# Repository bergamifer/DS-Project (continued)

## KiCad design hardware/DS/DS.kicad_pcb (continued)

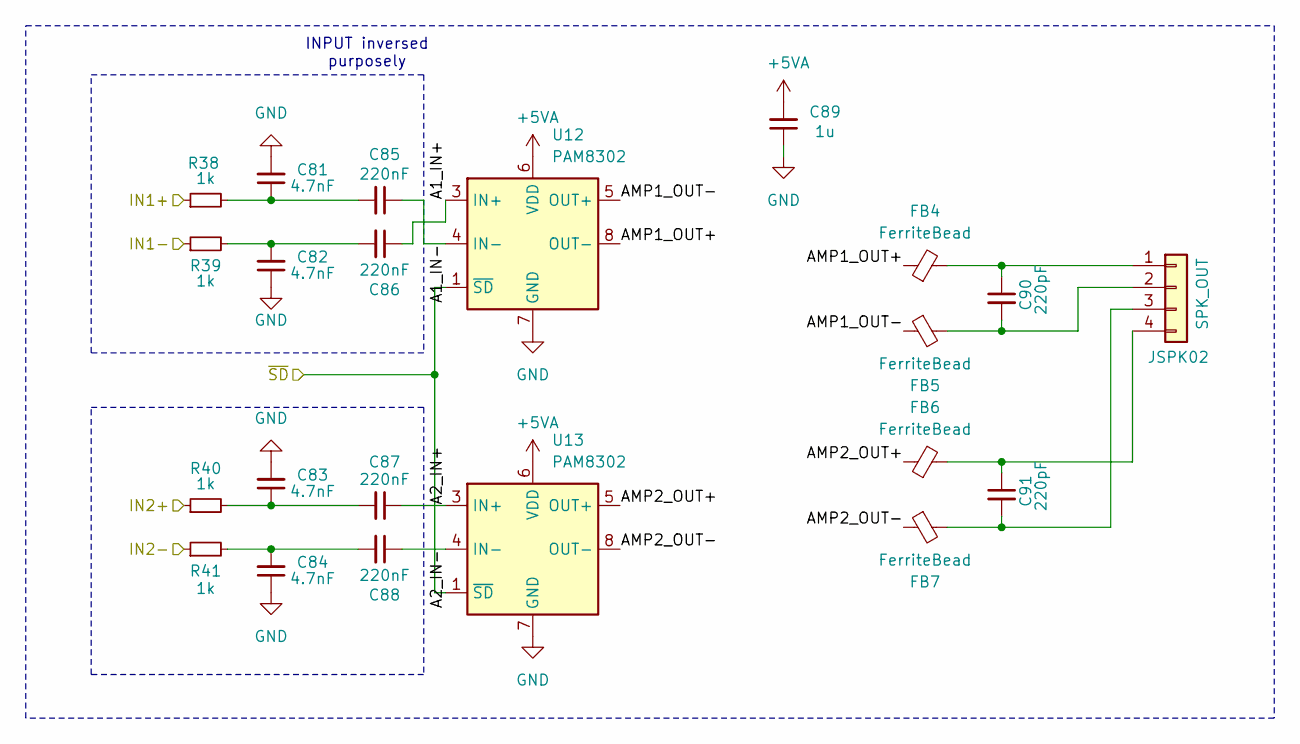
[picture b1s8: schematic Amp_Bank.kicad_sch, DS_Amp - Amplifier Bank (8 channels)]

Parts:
C81, C82, C83, C84: 4.7nF; C_0603_1608Metric; Manufacturer_Part_Number GCM1885C1H472GA16D; LCSC C2961271
C85, C86, C87, C88: 220nF; C_0402_1005Metric; Manufacturer_Part_Number CL05B224KO5NNNC; LCSC C16772
C89: 1u; C_0603_1608Metric; Mouser part 791-0603B105M160CT
C90, C91: 220pF; C_0402_1005Metric; Mouser part 581-KGM15BR71E104KT
FB4, FB5, FB6, FB7: FerriteBead; L_0805_2012Metric; Manufacturer_Part_Number SCBW201209U601T; LCSC C21286
JSPK02: SPK_OUT; JST_XH_B4B-XH-A_1x04_P2.50mm_Vertical; Manufacturer_Part_Number 8821WV-04KP; LCSC C5447988
R38, R39, R40, R41: 1k; R_0402_1005Metric; Manufacturer_Part_Number 0402WGF1001TCE; LCSC C11702
U12, U13: PAM8302; MSOP-8_3x3mm_P0.65mm; Manufacturer_Part_Number PAM8302AASCR; LCSC C113367

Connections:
+5VA: C89.2, U12.6 (VDD), U13.6 (VDD); also elsewhere on the board
/ALL_AMPS/Amp_Bank_A1/A1_IN+: C86.1, U12.3 (IN+)
/ALL_AMPS/Amp_Bank_A1/A1_IN-: C85.1, U12.4 (IN-)
/ALL_AMPS/Amp_Bank_A1/A2_IN+: C87.1, U13.3 (IN+)
/ALL_AMPS/Amp_Bank_A1/A2_IN-: C88.1, U13.4 (IN-)
/ALL_AMPS/Amp_Bank_A1/AMP1_OUT+: FB4.1, U12.8 (OUT-)
/ALL_AMPS/Amp_Bank_A1/AMP1_OUT-: FB5.1, U12.5 (OUT+)
/ALL_AMPS/Amp_Bank_A1/AMP2_OUT+: FB6.1, U13.5 (OUT+)
/ALL_AMPS/Amp_Bank_A1/AMP2_OUT-: FB7.1, U13.8 (OUT-)
/ALL_AMPS/SD: U12.1 (~SD), U13.1 (~SD); also elsewhere on the board
/ALL_AMPS/VA.N3: R39.1; also elsewhere on the board
/ALL_AMPS/VA.N4: R41.1; also elsewhere on the board
/ALL_AMPS/VA.P3: R38.1; also elsewhere on the board
/ALL_AMPS/VA.P4: R40.1; also elsewhere on the board
GND: C81.2, C82.1, C83.2, C84.1, C89.1, U12.7 (GND), U13.7 (GND); also elsewhere on the board
unnamed: C81.1, C85.2, R38.2
unnamed: C82.2, C86.2, R39.2
unnamed: C83.1, C87.2, R40.2
unnamed: C84.2, C88.2, R41.2
unnamed: C90.1, FB4.2, JSPK02.1
unnamed: C90.2, FB5.2, JSPK02.2
unnamed: C91.2, FB7.2, JSPK02.3
unnamed: C91.1, FB6.2, JSPK02.4

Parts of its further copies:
C92, C93, C94, C95, C103, C104, C105, C106, C114, C115, C116, C117, C125, C126, C127, C128, C136, C137, C138, C139, C147, C148, C149, C150, C158, C159, C160, C161, C169, C170, C171, C172, C180, C181, C182, C183, C191, C192, C193, C194, C202, C203, C204, C205, C213, C214, C215, C216, C224, C225, C226, C227, C235, C236, C237, C238, C246, C247, C248, C249: 4.7nF; C_0603_1608Metric; Manufacturer_Part_Number GCM1885C1H472GA16D; LCSC C2961271
C96, C97, C98, C99, C107, C108, C109, C110, C118, C119, C120, C121, C129, C130, C131, C132, C140, C141, C142, C143, C151, C152, C153, C154, C162, C163, C164, C165, C173, C174, C175, C176, C184, C185, C186, C187, C195, C196, C197, C198, C206, C207, C208, C209, C217, C218, C219, C220, C228, C229, C230, C231, C239, C240, C241, C242, C250, C251, C252, C253: 220nF; C_0402_1005Metric; Manufacturer_Part_Number CL05B224KO5NNNC; LCSC C16772
C100, C111, C122, C133, C144, C155, C166, C177, C188, C199, C210, C221, C232, C243, C254: 1u; C_0603_1608Metric; Mouser part 791-0603B105M160CT
C101, C102, C112, C113, C123, C124, C134, C135, C145, C146, C156, C157, C167, C168, C178, C179, C189, C190, C200, C201, C211, C212, C222, C223, C233, C234, C244, C245, C255, C256: 220pF; C_0402_1005Metric; Mouser part 581-KGM15BR71E104KT
FB8, FB9, FB10, FB11, FB12, FB13, FB14, FB15, FB16, FB17, FB18, FB19, FB20, FB21, FB22, FB23, FB24, FB25, FB26, FB27, FB28, FB29, FB30, FB31, FB32, FB33, FB34, FB35, FB36, FB37, FB38, FB39, FB40, FB41, FB42, FB43, FB44, FB45, FB46, FB47, FB48, FB49, FB50, FB51, FB52, FB53, FB54, FB55, FB56, FB57, FB58, FB59, FB60, FB61, FB62, FB63, FB64, FB65, FB66, FB67: FerriteBead; L_0805_2012Metric; Manufacturer_Part_Number SCBW201209U601T; LCSC C21286
JSPK01, JSPK03, JSPK04, JSPK05, JSPK06, JSPK07, JSPK08, JSPK09, JSPK10, JSPK11, JSPK12, JSPK13, JSPK14, JSPK15, JSPK16: SPK_OUT; JST_XH_B4B-XH-A_1x04_P2.50mm_Vertical; Manufacturer_Part_Number 8821WV-04KP; LCSC C5447988
R42, R43, R44, R45, R46, R47, R48, R49, R50, R51, R52, R53, R54, R55, R56, R57, R58, R59, R60, R61, R62, R63, R64, R65, R66, R67, R68, R69, R70, R71, R72, R73, R74, R75, R76, R77, R78, R79, R80, R81, R82, R83, R84, R85, R86, R87, R88, R89, R90, R91, R92, R93, R94, R95, R96, R97, R98, R99, R100, R101: 1k; R_0402_1005Metric; Manufacturer_Part_Number 0402WGF1001TCE; LCSC C11702
U14, U15, U16, U17, U18, U19, U20, U21, U22, U23, U24, U25, U26, U27, U28, U29, U30, U31, U32, U33, U34, U35, U36, U37, U38, U39, U40, U41, U42, U43: PAM8302; MSOP-8_3x3mm_P0.65mm; Manufacturer_Part_Number PAM8302AASCR; LCSC C113367

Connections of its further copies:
+5VA: C100.2, C111.2, C122.2, C133.2, C144.2, C155.2, C166.2, C177.2, C188.2, C199.2, C210.2, C221.2, C232.2, C243.2, C254.2, U14.6 (VDD), U15.6 (VDD), U16.6 (VDD), U17.6 (VDD), U18.6 (VDD), U19.6 (VDD), U20.6 (VDD), U21.6 (VDD), U22.6 (VDD), U23.6 (VDD), U24.6 (VDD), U25.6 (VDD), U26.6 (VDD), U27.6 (VDD), U28.6 (VDD), U29.6 (VDD), U30.6 (VDD), U31.6 (VDD), U32.6 (VDD), U33.6 (VDD), U34.6 (VDD), U35.6 (VDD), U36.6 (VDD), U37.6 (VDD), U38.6 (VDD), U39.6 (VDD), U40.6 (VDD), U41.6 (VDD), U42.6 (VDD), U43.6 (VDD); also elsewhere on the board
/ALL_AMPS/Amp_Bank_A2/A1_IN+: C97.1, U14.3 (IN+)
/ALL_AMPS/Amp_Bank_A2/A1_IN-: C96.1, U14.4 (IN-)
/ALL_AMPS/Amp_Bank_A2/A2_IN+: C98.1, U15.3 (IN+)
/ALL_AMPS/Amp_Bank_A2/A2_IN-: C99.1, U15.4 (IN-)
/ALL_AMPS/Amp_Bank_A2/AMP1_OUT+: FB8.1, U14.8 (OUT-)
/ALL_AMPS/Amp_Bank_A2/AMP1_OUT-: FB9.1, U14.5 (OUT+)
/ALL_AMPS/Amp_Bank_A2/AMP2_OUT+: FB10.1, U15.5 (OUT+)
/ALL_AMPS/Amp_Bank_A2/AMP2_OUT-: FB11.1, U15.8 (OUT-)
/ALL_AMPS/Amp_Bank_A3/A1_IN+: C108.1, U16.3 (IN+)
/ALL_AMPS/Amp_Bank_A3/A1_IN-: C107.1, U16.4 (IN-)
/ALL_AMPS/Amp_Bank_A3/A2_IN+: C109.1, U17.3 (IN+)
/ALL_AMPS/Amp_Bank_A3/A2_IN-: C110.1, U17.4 (IN-)
/ALL_AMPS/Amp_Bank_A3/AMP1_OUT+: FB12.1, U16.8 (OUT-)
/ALL_AMPS/Amp_Bank_A3/AMP1_OUT-: FB13.1, U16.5 (OUT+)
/ALL_AMPS/Amp_Bank_A3/AMP2_OUT+: FB14.1, U17.5 (OUT+)
/ALL_AMPS/Amp_Bank_A3/AMP2_OUT-: FB15.1, U17.8 (OUT-)
/ALL_AMPS/Amp_Bank_A4/A1_IN+: C119.1, U18.3 (IN+)
/ALL_AMPS/Amp_Bank_A4/A1_IN-: C118.1, U18.4 (IN-)
/ALL_AMPS/Amp_Bank_A4/A2_IN+: C120.1, U19.3 (IN+)
/ALL_AMPS/Amp_Bank_A4/A2_IN-: C121.1, U19.4 (IN-)
/ALL_AMPS/Amp_Bank_A4/AMP1_OUT+: FB16.1, U18.8 (OUT-)
/ALL_AMPS/Amp_Bank_A4/AMP1_OUT-: FB17.1, U18.5 (OUT+)
/ALL_AMPS/Amp_Bank_A4/AMP2_OUT+: FB18.1, U19.5 (OUT+)
/ALL_AMPS/Amp_Bank_A4/AMP2_OUT-: FB19.1, U19.8 (OUT-)
/ALL_AMPS/Amp_Bank_A5/A1_IN+: C130.1, U20.3 (IN+)
/ALL_AMPS/Amp_Bank_A5/A1_IN-: C129.1, U20.4 (IN-)
/ALL_AMPS/Amp_Bank_A5/A2_IN+: C131.1, U21.3 (IN+)
/ALL_AMPS/Amp_Bank_A5/A2_IN-: C132.1, U21.4 (IN-)
/ALL_AMPS/Amp_Bank_A5/AMP1_OUT+: FB20.1, U20.8 (OUT-)
/ALL_AMPS/Amp_Bank_A5/AMP1_OUT-: FB21.1, U20.5 (OUT+)
/ALL_AMPS/Amp_Bank_A5/AMP2_OUT+: FB22.1, U21.5 (OUT+)
/ALL_AMPS/Amp_Bank_A5/AMP2_OUT-: FB23.1, U21.8 (OUT-)
/ALL_AMPS/Amp_Bank_A6/A1_IN+: C141.1, U22.3 (IN+)
/ALL_AMPS/Amp_Bank_A6/A1_IN-: C140.1, U22.4 (IN-)
/ALL_AMPS/Amp_Bank_A6/A2_IN+: C142.1, U23.3 (IN+)
/ALL_AMPS/Amp_Bank_A6/A2_IN-: C143.1, U23.4 (IN-)
/ALL_AMPS/Amp_Bank_A6/AMP1_OUT+: FB24.1, U22.8 (OUT-)
/ALL_AMPS/Amp_Bank_A6/AMP1_OUT-: FB25.1, U22.5 (OUT+)
/ALL_AMPS/Amp_Bank_A6/AMP2_OUT+: FB26.1, U23.5 (OUT+)
/ALL_AMPS/Amp_Bank_A6/AMP2_OUT-: FB27.1, U23.8 (OUT-)
/ALL_AMPS/Amp_Bank_A7/A1_IN+: C152.1, U24.3 (IN+)
/ALL_AMPS/Amp_Bank_A7/A1_IN-: C151.1, U24.4 (IN-)
/ALL_AMPS/Amp_Bank_A7/A2_IN+: C153.1, U25.3 (IN+)
/ALL_AMPS/Amp_Bank_A7/A2_IN-: C154.1, U25.4 (IN-)
/ALL_AMPS/Amp_Bank_A7/AMP1_OUT+: FB28.1, U24.8 (OUT-)
/ALL_AMPS/Amp_Bank_A7/AMP1_OUT-: FB29.1, U24.5 (OUT+)
/ALL_AMPS/Amp_Bank_A7/AMP2_OUT+: FB30.1, U25.5 (OUT+)
/ALL_AMPS/Amp_Bank_A7/AMP2_OUT-: FB31.1, U25.8 (OUT-)
/ALL_AMPS/Amp_Bank_A8/A1_IN+: C163.1, U26.3 (IN+)
/ALL_AMPS/Amp_Bank_A8/A1_IN-: C162.1, U26.4 (IN-)
/ALL_AMPS/Amp_Bank_A8/A2_IN+: C164.1, U27.3 (IN+)
/ALL_AMPS/Amp_Bank_A8/A2_IN-: C165.1, U27.4 (IN-)
/ALL_AMPS/Amp_Bank_A8/AMP1_OUT+: FB32.1, U26.8 (OUT-)
/ALL_AMPS/Amp_Bank_A8/AMP1_OUT-: FB33.1, U26.5 (OUT+)
/ALL_AMPS/Amp_Bank_A8/AMP2_OUT+: FB34.1, U27.5 (OUT+)
/ALL_AMPS/Amp_Bank_A8/AMP2_OUT-: FB35.1, U27.8 (OUT-)
/ALL_AMPS/Amp_Bank_A9/A1_IN+: C174.1, U28.3 (IN+)
/ALL_AMPS/Amp_Bank_A9/A1_IN-: C173.1, U28.4 (IN-)
/ALL_AMPS/Amp_Bank_A9/A2_IN+: C175.1, U29.3 (IN+)
/ALL_AMPS/Amp_Bank_A9/A2_IN-: C176.1, U29.4 (IN-)
/ALL_AMPS/Amp_Bank_A9/AMP1_OUT+: FB36.1, U28.8 (OUT-)
/ALL_AMPS/Amp_Bank_A9/AMP1_OUT-: FB37.1, U28.5 (OUT+)
/ALL_AMPS/Amp_Bank_A9/AMP2_OUT+: FB38.1, U29.5 (OUT+)
/ALL_AMPS/Amp_Bank_A9/AMP2_OUT-: FB39.1, U29.8 (OUT-)
/ALL_AMPS/Amp_Bank_A10/A1_IN+: C185.1, U30.3 (IN+)
/ALL_AMPS/Amp_Bank_A10/A1_IN-: C184.1, U30.4 (IN-)
/ALL_AMPS/Amp_Bank_A10/A2_IN+: C186.1, U31.3 (IN+)
/ALL_AMPS/Amp_Bank_A10/A2_IN-: C187.1, U31.4 (IN-)
/ALL_AMPS/Amp_Bank_A10/AMP1_OUT+: FB40.1, U30.8 (OUT-)
/ALL_AMPS/Amp_Bank_A10/AMP1_OUT-: FB41.1, U30.5 (OUT+)
/ALL_AMPS/Amp_Bank_A10/AMP2_OUT+: FB42.1, U31.5 (OUT+)
/ALL_AMPS/Amp_Bank_A10/AMP2_OUT-: FB43.1, U31.8 (OUT-)
/ALL_AMPS/Amp_Bank_A11/A1_IN+: C196.1, U32.3 (IN+)
/ALL_AMPS/Amp_Bank_A11/A1_IN-: C195.1, U32.4 (IN-)
/ALL_AMPS/Amp_Bank_A11/A2_IN+: C197.1, U33.3 (IN+)
/ALL_AMPS/Amp_Bank_A11/A2_IN-: C198.1, U33.4 (IN-)
/ALL_AMPS/Amp_Bank_A11/AMP1_OUT+: FB44.1, U32.8 (OUT-)
/ALL_AMPS/Amp_Bank_A11/AMP1_OUT-: FB45.1, U32.5 (OUT+)
/ALL_AMPS/Amp_Bank_A11/AMP2_OUT+: FB46.1, U33.5 (OUT+)
/ALL_AMPS/Amp_Bank_A11/AMP2_OUT-: FB47.1, U33.8 (OUT-)
/ALL_AMPS/Amp_Bank_A12/A1_IN+: C207.1, U34.3 (IN+)
/ALL_AMPS/Amp_Bank_A12/A1_IN-: C206.1, U34.4 (IN-)
/ALL_AMPS/Amp_Bank_A12/A2_IN+: C208.1, U35.3 (IN+)
/ALL_AMPS/Amp_Bank_A12/A2_IN-: C209.1, U35.4 (IN-)
/ALL_AMPS/Amp_Bank_A12/AMP1_OUT+: FB48.1, U34.8 (OUT-)
/ALL_AMPS/Amp_Bank_A12/AMP1_OUT-: FB49.1, U34.5 (OUT+)
/ALL_AMPS/Amp_Bank_A12/AMP2_OUT+: FB50.1, U35.5 (OUT+)
/ALL_AMPS/Amp_Bank_A12/AMP2_OUT-: FB51.1, U35.8 (OUT-)
/ALL_AMPS/Amp_Bank_A13/A1_IN+: C218.1, U36.3 (IN+)
/ALL_AMPS/Amp_Bank_A13/A1_IN-: C217.1, U36.4 (IN-)
/ALL_AMPS/Amp_Bank_A13/A2_IN+: C219.1, U37.3 (IN+)
/ALL_AMPS/Amp_Bank_A13/A2_IN-: C220.1, U37.4 (IN-)
/ALL_AMPS/Amp_Bank_A13/AMP1_OUT+: FB52.1, U36.8 (OUT-)
/ALL_AMPS/Amp_Bank_A13/AMP1_OUT-: FB53.1, U36.5 (OUT+)
/ALL_AMPS/Amp_Bank_A13/AMP2_OUT+: FB54.1, U37.5 (OUT+)
/ALL_AMPS/Amp_Bank_A13/AMP2_OUT-: FB55.1, U37.8 (OUT-)
/ALL_AMPS/Amp_Bank_A14/A1_IN+: C229.1, U38.3 (IN+)
/ALL_AMPS/Amp_Bank_A14/A1_IN-: C228.1, U38.4 (IN-)
/ALL_AMPS/Amp_Bank_A14/A2_IN+: C230.1, U39.3 (IN+)
/ALL_AMPS/Amp_Bank_A14/A2_IN-: C231.1, U39.4 (IN-)
/ALL_AMPS/Amp_Bank_A14/AMP1_OUT+: FB56.1, U38.8 (OUT-)
/ALL_AMPS/Amp_Bank_A14/AMP1_OUT-: FB57.1, U38.5 (OUT+)
/ALL_AMPS/Amp_Bank_A14/AMP2_OUT+: FB58.1, U39.5 (OUT+)
/ALL_AMPS/Amp_Bank_A14/AMP2_OUT-: FB59.1, U39.8 (OUT-)
/ALL_AMPS/Amp_Bank_A15/A1_IN+: C240.1, U40.3 (IN+)
/ALL_AMPS/Amp_Bank_A15/A1_IN-: C239.1, U40.4 (IN-)
/ALL_AMPS/Amp_Bank_A15/A2_IN+: C241.1, U41.3 (IN+)
/ALL_AMPS/Amp_Bank_A15/A2_IN-: C242.1, U41.4 (IN-)
/ALL_AMPS/Amp_Bank_A15/AMP1_OUT+: FB60.1, U40.8 (OUT-)
/ALL_AMPS/Amp_Bank_A15/AMP1_OUT-: FB61.1, U40.5 (OUT+)
/ALL_AMPS/Amp_Bank_A15/AMP2_OUT+: FB62.1, U41.5 (OUT+)
/ALL_AMPS/Amp_Bank_A15/AMP2_OUT-: FB63.1, U41.8 (OUT-)
/ALL_AMPS/Amp_Bank_A16/A1_IN+: C251.1, U42.3 (IN+)
/ALL_AMPS/Amp_Bank_A16/A1_IN-: C250.1, U42.4 (IN-)
/ALL_AMPS/Amp_Bank_A16/A2_IN+: C252.1, U43.3 (IN+)
/ALL_AMPS/Amp_Bank_A16/A2_IN-: C253.1, U43.4 (IN-)
/ALL_AMPS/Amp_Bank_A16/AMP1_OUT+: FB64.1, U42.8 (OUT-)
/ALL_AMPS/Amp_Bank_A16/AMP1_OUT-: FB65.1, U42.5 (OUT+)
/ALL_AMPS/Amp_Bank_A16/AMP2_OUT+: FB66.1, U43.5 (OUT+)
/ALL_AMPS/Amp_Bank_A16/AMP2_OUT-: FB67.1, U43.8 (OUT-)
/ALL_AMPS/SD: U14.1 (~SD), U15.1 (~SD), U16.1 (~SD), U17.1 (~SD), U18.1 (~SD), U19.1 (~SD), U20.1 (~SD), U21.1 (~SD), U22.1 (~SD), U23.1 (~SD), U24.1 (~SD), U25.1 (~SD), U26.1 (~SD), U27.1 (~SD), U28.1 (~SD), U29.1 (~SD), U30.1 (~SD), U31.1 (~SD), U32.1 (~SD), U33.1 (~SD), U34.1 (~SD), U35.1 (~SD), U36.1 (~SD), U37.1 (~SD), U38.1 (~SD), U39.1 (~SD), U40.1 (~SD), U41.1 (~SD), U42.1 (~SD), U43.1 (~SD); also elsewhere on the board
/ALL_AMPS/VA.N1: R99.1; also elsewhere on the board
/ALL_AMPS/VA.N2: R101.1; also elsewhere on the board
/ALL_AMPS/VA.N5: R43.1; also elsewhere on the board
/ALL_AMPS/VA.N6: R45.1; also elsewhere on the board
/ALL_AMPS/VA.N7: R47.1; also elsewhere on the board
/ALL_AMPS/VA.N8: R49.1; also elsewhere on the board
/ALL_AMPS/VA.P1: R98.1; also elsewhere on the board
/ALL_AMPS/VA.P2: R100.1; also elsewhere on the board
/ALL_AMPS/VA.P5: R42.1; also elsewhere on the board
/ALL_AMPS/VA.P6: R44.1; also elsewhere on the board
/ALL_AMPS/VA.P7: R46.1; also elsewhere on the board
/ALL_AMPS/VA.P8: R48.1; also elsewhere on the board
/ALL_AMPS/VB.N1: R51.1; also elsewhere on the board
/ALL_AMPS/VB.N2: R53.1; also elsewhere on the board
/ALL_AMPS/VB.N3: R55.1; also elsewhere on the board
/ALL_AMPS/VB.N4: R57.1; also elsewhere on the board
/ALL_AMPS/VB.N5: R59.1; also elsewhere on the board
/ALL_AMPS/VB.N6: R61.1; also elsewhere on the board
/ALL_AMPS/VB.N7: R63.1; also elsewhere on the board
/ALL_AMPS/VB.N8: R65.1; also elsewhere on the board
/ALL_AMPS/VB.P1: R50.1; also elsewhere on the board
/ALL_AMPS/VB.P2: R52.1; also elsewhere on the board
/ALL_AMPS/VB.P3: R54.1; also elsewhere on the board
/ALL_AMPS/VB.P4: R56.1; also elsewhere on the board
/ALL_AMPS/VB.P5: R58.1; also elsewhere on the board
/ALL_AMPS/VB.P6: R60.1; also elsewhere on the board
/ALL_AMPS/VB.P7: R62.1; also elsewhere on the board
/ALL_AMPS/VB.P8: R64.1; also elsewhere on the board
/ALL_AMPS/VC.N1: R67.1; also elsewhere on the board
/ALL_AMPS/VC.N2: R69.1; also elsewhere on the board
/ALL_AMPS/VC.N3: R71.1; also elsewhere on the board
/ALL_AMPS/VC.N4: R73.1; also elsewhere on the board
/ALL_AMPS/VC.N5: R75.1; also elsewhere on the board
/ALL_AMPS/VC.N6: R77.1; also elsewhere on the board
/ALL_AMPS/VC.N7: R79.1; also elsewhere on the board
/ALL_AMPS/VC.N8: R81.1; also elsewhere on the board
/ALL_AMPS/VC.P1: R66.1; also elsewhere on the board
/ALL_AMPS/VC.P2: R68.1; also elsewhere on the board
/ALL_AMPS/VC.P3: R70.1; also elsewhere on the board
/ALL_AMPS/VC.P4: R72.1; also elsewhere on the board
/ALL_AMPS/VC.P5: R74.1; also elsewhere on the board
/ALL_AMPS/VC.P6: R76.1; also elsewhere on the board
/ALL_AMPS/VC.P7: R78.1; also elsewhere on the board
/ALL_AMPS/VC.P8: R80.1; also elsewhere on the board
/ALL_AMPS/VD.N1: R83.1; also elsewhere on the board
/ALL_AMPS/VD.N2: R85.1; also elsewhere on the board
/ALL_AMPS/VD.N3: R87.1; also elsewhere on the board
/ALL_AMPS/VD.N4: R89.1; also elsewhere on the board
/ALL_AMPS/VD.N5: R91.1; also elsewhere on the board
/ALL_AMPS/VD.N6: R93.1; also elsewhere on the board
/ALL_AMPS/VD.N7: R95.1; also elsewhere on the board
/ALL_AMPS/VD.N8: R97.1; also elsewhere on the board
/ALL_AMPS/VD.P1: R82.1; also elsewhere on the board
/ALL_AMPS/VD.P2: R84.1; also elsewhere on the board
/ALL_AMPS/VD.P3: R86.1; also elsewhere on the board
/ALL_AMPS/VD.P4: R88.1; also elsewhere on the board
/ALL_AMPS/VD.P5: R90.1; also elsewhere on the board
/ALL_AMPS/VD.P6: R92.1; also elsewhere on the board
/ALL_AMPS/VD.P7: R94.1; also elsewhere on the board
/ALL_AMPS/VD.P8: R96.1; also elsewhere on the board
GND: C92.2, C93.1, C94.2, C95.1, C100.1, C103.2, C104.1, C105.2, C106.1, C111.1, C114.2, C115.1, C116.2, C117.1, C122.1, C125.2, C126.1, C127.2, C128.1, C133.1, C136.2, C137.1, C138.2, C139.1, C144.1, C147.2, C148.1, C149.2, C150.1, C155.1, C158.2, C159.1, C160.2, C161.1, C166.1, C169.2, C170.1, C171.2, C172.1, C177.1, C180.2, C181.1, C182.2, C183.1, C188.1, C191.2, C192.1, C193.2, C194.1, C199.1, C202.2, C203.1, C204.2, C205.1, C210.1, C213.2, C214.1, C215.2, C216.1, C221.1, C224.2, C225.1, C226.2, C227.1, C232.1, C235.2, C236.1, C237.2, C238.1, C243.1, C246.2, C247.1, C248.2, C249.1, C254.1, U14.7 (GND), U15.7 (GND), U16.7 (GND), U17.7 (GND), U18.7 (GND), U19.7 (GND), U20.7 (GND), U21.7 (GND), U22.7 (GND), U23.7 (GND), U24.7 (GND), U25.7 (GND), U26.7 (GND), U27.7 (GND), U28.7 (GND), U29.7 (GND), U30.7 (GND), U31.7 (GND), U32.7 (GND), U33.7 (GND), U34.7 (GND), U35.7 (GND), U36.7 (GND), U37.7 (GND), U38.7 (GND), U39.7 (GND), U40.7 (GND), U41.7 (GND), U42.7 (GND), U43.7 (GND); also elsewhere on the board
unnamed: C92.1, C96.2, R42.2
unnamed: C93.2, C97.2, R43.2
unnamed: C94.1, C98.2, R44.2
unnamed: C95.2, C99.2, R45.2
unnamed: C103.1, C107.2, R46.2
unnamed: C104.2, C108.2, R47.2
unnamed: C105.1, C109.2, R48.2
unnamed: C106.2, C110.2, R49.2
unnamed: C114.1, C118.2, R50.2
unnamed: C115.2, C119.2, R51.2
unnamed: C116.1, C120.2, R52.2
unnamed: C117.2, C121.2, R53.2
unnamed: C125.1, C129.2, R54.2
unnamed: C126.2, C130.2, R55.2
unnamed: C127.1, C131.2, R56.2
unnamed: C128.2, C132.2, R57.2
unnamed: C136.1, C140.2, R58.2
unnamed: C137.2, C141.2, R59.2
unnamed: C138.1, C142.2, R60.2
unnamed: C139.2, C143.2, R61.2
unnamed: C147.1, C151.2, R62.2
unnamed: C148.2, C152.2, R63.2
unnamed: C149.1, C153.2, R64.2
unnamed: C150.2, C154.2, R65.2
unnamed: C158.1, C162.2, R66.2
unnamed: C159.2, C163.2, R67.2
unnamed: C160.1, C164.2, R68.2
unnamed: C161.2, C165.2, R69.2
unnamed: C169.1, C173.2, R70.2
unnamed: C170.2, C174.2, R71.2
unnamed: C171.1, C175.2, R72.2
unnamed: C172.2, C176.2, R73.2
unnamed: C180.1, C184.2, R74.2
unnamed: C181.2, C185.2, R75.2
unnamed: C182.1, C186.2, R76.2
unnamed: C183.2, C187.2, R77.2
unnamed: C191.1, C195.2, R78.2
unnamed: C192.2, C196.2, R79.2
unnamed: C193.1, C197.2, R80.2
unnamed: C194.2, C198.2, R81.2
unnamed: C202.1, C206.2, R82.2
unnamed: C203.2, C207.2, R83.2
unnamed: C204.1, C208.2, R84.2
unnamed: C205.2, C209.2, R85.2
unnamed: C213.1, C217.2, R86.2
unnamed: C214.2, C218.2, R87.2
unnamed: C215.1, C219.2, R88.2
unnamed: C216.2, C220.2, R89.2
unnamed: C224.1, C228.2, R90.2
unnamed: C225.2, C229.2, R91.2
unnamed: C226.1, C230.2, R92.2
unnamed: C227.2, C231.2, R93.2
unnamed: C235.1, C239.2, R94.2
unnamed: C236.2, C240.2, R95.2
unnamed: C237.1, C241.2, R96.2
unnamed: C238.2, C242.2, R97.2
unnamed: C246.1, C250.2, R98.2
unnamed: C247.2, C251.2, R99.2
unnamed: C248.1, C252.2, R100.2
unnamed: C249.2, C253.2, R101.2
unnamed: C255.1, FB64.2, JSPK01.1
unnamed: C255.2, FB65.2, JSPK01.2
unnamed: C256.2, FB67.2, JSPK01.3
unnamed: C256.1, FB66.2, JSPK01.4
unnamed: C101.1, FB8.2, JSPK03.1
unnamed: C101.2, FB9.2, JSPK03.2
unnamed: C102.2, FB11.2, JSPK03.3
unnamed: C102.1, FB10.2, JSPK03.4
unnamed: C112.1, FB12.2, JSPK04.1
unnamed: C112.2, FB13.2, JSPK04.2
unnamed: C113.2, FB15.2, JSPK04.3
unnamed: C113.1, FB14.2, JSPK04.4
unnamed: C123.1, FB16.2, JSPK05.1
unnamed: C123.2, FB17.2, JSPK05.2
unnamed: C124.2, FB19.2, JSPK05.3
unnamed: C124.1, FB18.2, JSPK05.4
unnamed: C134.1, FB20.2, JSPK06.1
unnamed: C134.2, FB21.2, JSPK06.2
unnamed: C135.2, FB23.2, JSPK06.3
unnamed: C135.1, FB22.2, JSPK06.4
unnamed: C145.1, FB24.2, JSPK07.1
unnamed: C145.2, FB25.2, JSPK07.2
unnamed: C146.2, FB27.2, JSPK07.3
unnamed: C146.1, FB26.2, JSPK07.4
unnamed: C156.1, FB28.2, JSPK08.1
unnamed: C156.2, FB29.2, JSPK08.2
unnamed: C157.2, FB31.2, JSPK08.3
unnamed: C157.1, FB30.2, JSPK08.4
unnamed: C178.1, FB36.2, JSPK09.1
unnamed: C178.2, FB37.2, JSPK09.2
unnamed: C179.2, FB39.2, JSPK09.3
unnamed: C179.1, FB38.2, JSPK09.4
unnamed: C167.1, FB32.2, JSPK10.1
unnamed: C167.2, FB33.2, JSPK10.2
unnamed: C168.2, FB35.2, JSPK10.3
unnamed: C168.1, FB34.2, JSPK10.4
unnamed: C189.1, FB40.2, JSPK11.1
unnamed: C189.2, FB41.2, JSPK11.2
unnamed: C190.2, FB43.2, JSPK11.3
unnamed: C190.1, FB42.2, JSPK11.4
unnamed: C200.1, FB44.2, JSPK12.1
unnamed: C200.2, FB45.2, JSPK12.2
unnamed: C201.2, FB47.2, JSPK12.3
unnamed: C201.1, FB46.2, JSPK12.4
unnamed: C211.1, FB48.2, JSPK13.1
unnamed: C211.2, FB49.2, JSPK13.2
unnamed: C212.2, FB51.2, JSPK13.3
unnamed: C212.1, FB50.2, JSPK13.4
unnamed: C222.1, FB52.2, JSPK14.1
unnamed: C222.2, FB53.2, JSPK14.2
unnamed: C223.2, FB55.2, JSPK14.3
unnamed: C223.1, FB54.2, JSPK14.4
unnamed: C233.1, FB56.2, JSPK15.1
unnamed: C233.2, FB57.2, JSPK15.2
unnamed: C234.2, FB59.2, JSPK15.3
unnamed: C234.1, FB58.2, JSPK15.4
unnamed: C244.1, FB60.2, JSPK16.1
unnamed: C244.2, FB61.2, JSPK16.2
unnamed: C245.2, FB63.2, JSPK16.3
unnamed: C245.1, FB62.2, JSPK16.4

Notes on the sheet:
INPUT inversed purposely

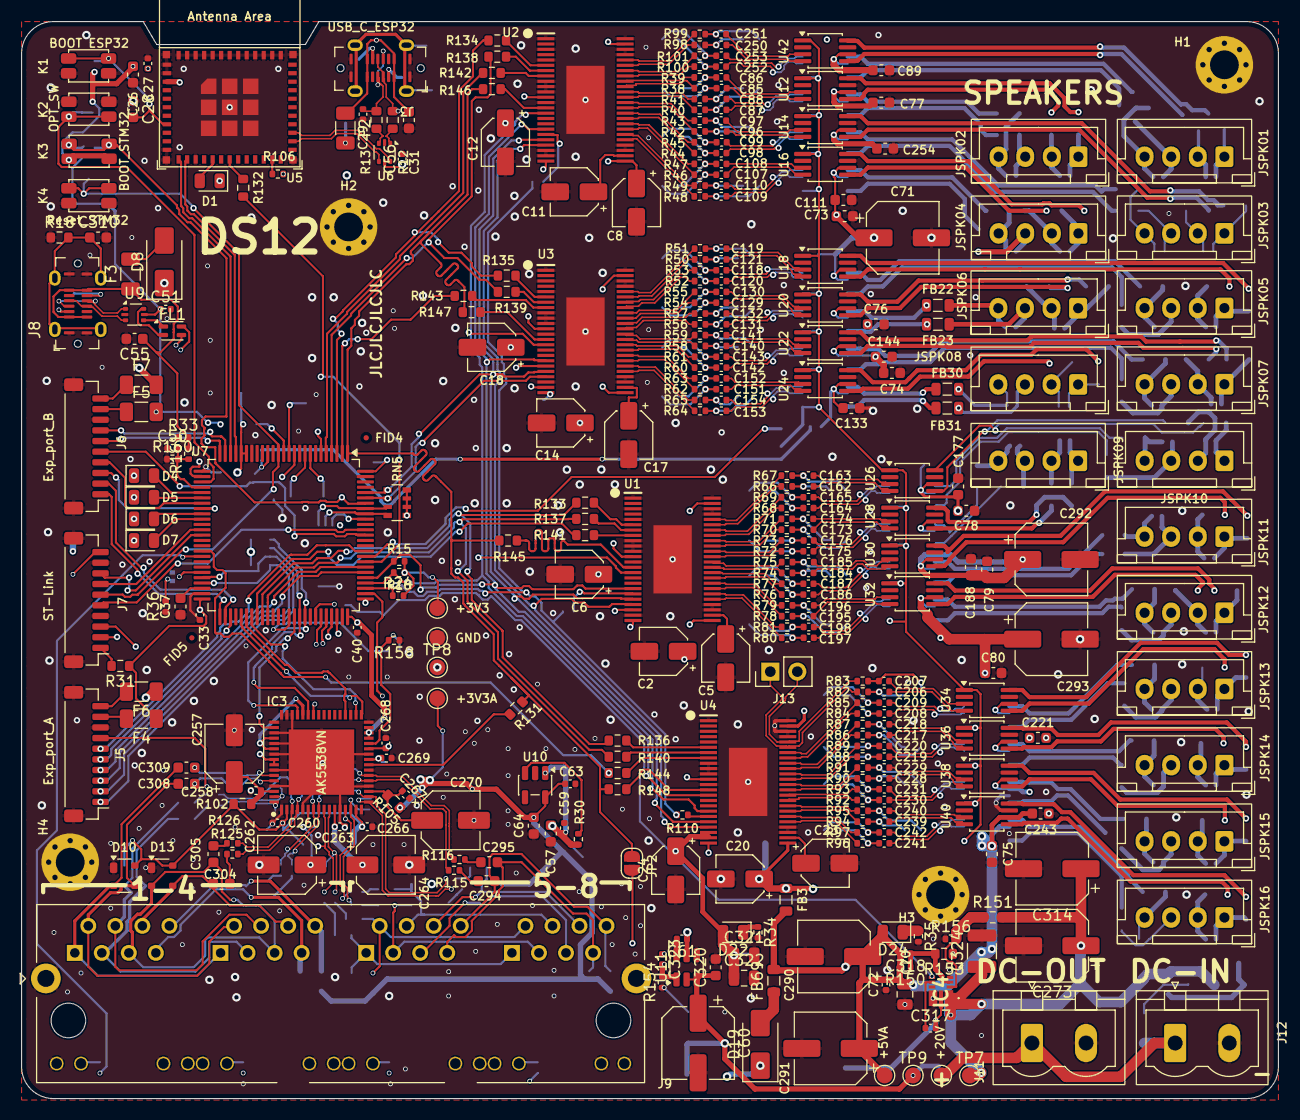
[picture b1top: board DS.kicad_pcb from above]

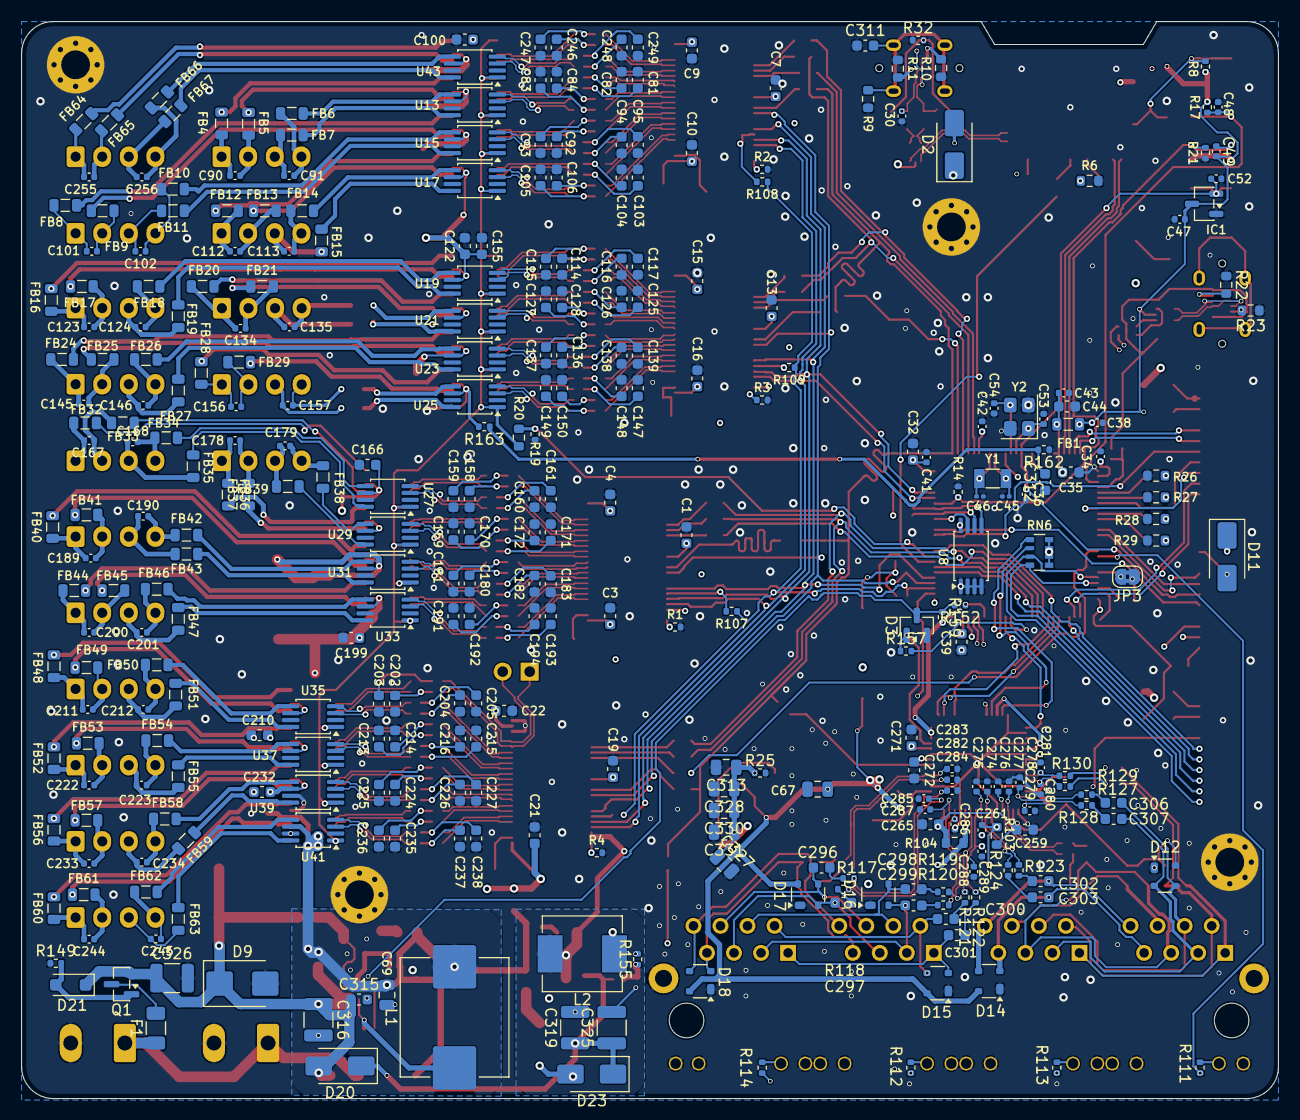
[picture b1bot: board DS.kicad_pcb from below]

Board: 4 copper layers, 118.1 x 101.2 mm, 681 parts (329 on the bottom side), 536 nets.

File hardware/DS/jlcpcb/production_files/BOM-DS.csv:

Comment,Designator,Footprint,LCSC,Quantity
0.1uF,"C258,C260,C261,C263,C266,C267,C268,C269,C27,C28,C33,C34,C36,C38,C40,C41,C42,C43,C47,C48,C49,C52,C58,C59,C61,C63,C65,C66,C68,C72",C_0402_1005Metric,C1525,30
10,R37,R_0402_1005Metric,C25077,1
100,R28,R_0603_1608Metric,C177347,1
100k,"R30,R35",R_0402_1005Metric,C25741,2
100pF,"C274,C275,C276,C277,C278,C279,C280,C281,C282,C283,C284,C285,C286,C287,C288,C289",C_0402_1005Metric,C327198,16
100uF,"C257,C262,C264,C270",CP_Elec_5x5.4,C18221491,4
10k,"R106,R14,R15,R16,R17,R21,R8",R_0402_1005Metric,C25744,7
10u EL,"C11,C12,C14,C17,C18,C2,C20,C23,C24,C5,C6,C60,C8",CP_Elec_4x5.7,C134745,13
10u cer,"C259,C26,C265,C272,C44,C73,C74,C75,C76,C77,C78,C79,C80",C_0603_1608Metric,C1691,13
150,"R27,R6",R_0603_1608Metric,C22808,2
18pF,"C53,C54",C_0402_1005Metric,C1549,2
1M,R9,R_0603_1608Metric,C22935,1
1k,"R1,R100,R101,R107,R108,R109,R110,R19,R2,R3,R38,R39,R4,R40,R41,R42,R43,R44,R45,R46,R47,R48,R49,R50,R51,R52,R53,R54,R55,R56,R57,R58,R59,R60,R61,R62,R63,R64,R65,R66,R67,R68,R69,R70,R71,R72,R73,R74,R75,R76,R77,R78,R79,R80,R81,R82,R83,R84,R85,R86,R87,R88,R89,R90,R91,R92,R93,R94,R95,R96,R97,R98,R99",R_0402_1005Metric,C11702,73
1u,"C1,C10,C100,C111,C122,C13,C133,C144,C15,C155,C16,C166,C177,C188,C19,C199,C21,C210,C22,C221,C232,C243,C254,C3,C35,C4,C57,C7,C89,C9",C_0603_1608Metric,C15849,30
2.2u,"C294,C295,C296,C297,C298,C299,C300,C301,C302,C303,C304,C305,C306,C307,C308,C309,C37,C39",C_0603_1608Metric,C23630,18
20,"R102,R103,R104,R105",R_0603_1608Metric,C22950,4
200,"R132,R26",R_0603_1608Metric,C8218,2
20k,R31,R_0402_1005Metric,C25765,1
220nF,"C107,C108,C109,C110,C118,C119,C120,C121,C129,C130,C131,C132,C140,C141,C142,C143,C151,C152,C153,C154,C162,C163,C164,C165,C173,C174,C175,C176,C184,C185,C186,C187,C195,C196,C197,C198,C206,C207,C208,C209,C217,C218,C219,C220,C228,C229,C230,C231,C239,C240,C241,C242,C250,C251,C252,C253,C85,C86,C87,C88,C96,C97,C98,C99",C_0402_1005Metric,C16772,64
220pF,"C101,C102,C112,C113,C123,C124,C134,C135,C145,C146,C156,C157,C167,C168,C178,C179,C189,C190,C200,C201,C211,C212,C222,C223,C233,C234,C244,C245,C255,C256,C90,C91",C_0402_1005Metric,C39122,32
220uF x16V,"C290,C291,C292,C293,C71",CP_Elec_6.3x7.7,C25503905,5
22p,"C29,C30",C_0402_1005Metric,C1555,2
22uF 50V,C56,CP_Elec_6.3x5.4,C72505,1
"22µF, 16V, X5R, 0805","C273,C67,C69,C70",C_0805_2012Metric,C45783,4
25MHz 12pF,Y2,Crystal_SMD_3225-4Pin_3.2x2.5mm,C9006,1
32.768K 7pF,Y1,Crystal_SMD_3215-2Pin_3.2x1.5mm,C280830,1
33,"R12,R13,R131,R20",R_0603_1608Metric,C23140,4
33pF,C62,C_0402_1005Metric,C1562,1
4.7k,"RN5,RN6",R_Array_Convex_4x0603,C1980,2
4.7nF,"C103,C104,C105,C106,C114,C115,C116,C117,C125,C126,C127,C128,C136,C137,C138,C139,C147,C148,C149,C150,C158,C159,C160,C161,C169,C170,C171,C172,C180,C181,C182,C183,C191,C192,C193,C194,C202,C203,C204,C205,C213,C214,C215,C216,C224,C225,C226,C227,C235,C236,C237,C238,C246,C247,C248,C249,C81,C82,C83,C84,C92,C93,C94,C95",C_0603_1608Metric,C2961271,64
4.7u,"C271,C31,C32,C64",C_0603_1608Metric,C19666,4
4.7uH,L1,L_Sunlord_MWSA0603S,C408447,1
40.2k,R34,R_0402_1005Metric,C2933097,1
470,"R111,R112,R113,R114,R115,R116,R117,R118,R119,R120,R121,R122,R123,R124,R125,R126,R127,R128,R129,R130",R_0402_1005Metric,C25117,20
470k,R33,R_0603_1608Metric,C23178,1
5.1k,"R10,R11",R_0603_1608Metric,C23186,2
7.5k,R32,R_0603_1608Metric,C23234,1
75,"R133,R134,R135,R136,R137,R138,R139,R140,R141,R142,R143,R144,R145,R146,R147,R148,R29",R_0603_1608Metric,C4275,17
8.2pF,"C45,C46",C_0201_0603Metric,C115571,2
8P8C_LED_Shielded x4,J9,RJ45_Amphenol_RJHSE538X-04,C7205134,1
9.09k,R36,R_0603_1608Metric,C2930134,1
AK5538VN,IC3,QFN50P900X900X100-65N,C2667106,1
AP1117-33,U11,SOT-223-3_TabPin2,C6186,1
AP2125,U10,SOT-23-5,C110463,1
B5819W SL,"D11,D2",D_SOD-123,C8598,2
BOOT ESP32,K1,SW_SPST_EVQP2_MiddlePushTravel_H2.5mm,C51927445,1
BOOT_STM32,K3,SW_SPST_EVQP2_MiddlePushTravel_H2.5mm,C51927445,1
CAT24C256,U8,TSSOP-8_4.4x3mm_P0.65mm,C146734,1
Conn_01x02,"J11,J12","PhoenixContact_MSTBVA_2,5_2-G-5,08_1x02_P5.08mm_Vertical",C41784016,2
ESP32-C3-MINI-1,U5,ESP32-C3-MINI-1,C2838502,1
Exp_port_A,J5,JST_SH_BM10B-SRSS-TB_1x10-1MP_P1.00mm_Vertical,C5343037,1
Exp_port_B,J6,JST_SH_BM10B-SRSS-TB_1x10-1MP_P1.00mm_Vertical,C5343037,1
FerriteBead,"FB1,FB10,FB11,FB12,FB13,FB14,FB15,FB16,FB17,FB18,FB19,FB2,FB20,FB21,FB22,FB23,FB24,FB25,FB26,FB27,FB28,FB29,FB3,FB30,FB31,FB32,FB33,FB34,FB35,FB36,FB37,FB38,FB39,FB4,FB40,FB41,FB42,FB43,FB44,FB45,FB46,FB47,FB48,FB49,FB5,FB50,FB51,FB52,FB53,FB54,FB55,FB56,FB57,FB58,FB59,FB6,FB60,FB61,FB62,FB63,FB64,FB65,FB66,FB67,FB7,FB8,FB9",L_0805_2012Metric,C21286,67
Green LED,D6,LED_0805_2012Metric,C2297,1
MAX809TEUR+T,IC1,SOT-23-3,C16711,1
MP2315SGJ-P,IC2,SOT65P280X100-8N,C3031493,1
OPT_SW,K2,SW_SPST_EVQP2_MiddlePushTravel_H2.5mm,C51927445,1
PAM8302,"U12,U13,U14,U15,U16,U17,U18,U19,U20,U21,U22,U23,U24,U25,U26,U27,U28,U29,U30,U31,U32,U33,U34,U35,U36,U37,U38,U39,U40,U41,U42,U43",MSOP-8_3x3mm_P0.65mm,C113367,32
PCM1690,"U1,U2,U3,U4",SOP50P810X120-49N,C181276,4
PRTR5V0U2X,"D10,D12,D13,D14,D15,D16,D17,D18",SOT-143,C5158049,8
Red LED,"D1,D5",LED_0805_2012Metric,C84256,2
Reset_STM32,K4,SW_SPST_EVQP2_MiddlePushTravel_H2.5mm,C51927445,1
SMBJ24A,D8,D_SMB,C908801,1
SPK_OUT,"JSPK01,JSPK02,JSPK03,JSPK04,JSPK05,JSPK06,JSPK07,JSPK08,JSPK09,JSPK10,JSPK11,JSPK12,JSPK13,JSPK14,JSPK15,JSPK16",JST_XH_B4B-XH-A_1x04_P2.50mm_Vertical,C5447988,16
SS34,D9,D_SMB,C8678,1
ST-Link,J7,JST_SH_BM10B-SRSS-TB_1x10-1MP_P1.00mm_Vertical,C5343037,1
STM32H743VITx,U7,LQFP-100_14x14mm_P0.5mm,C114409,1
USBLC6-2P6,U6,SOT-666,C15999,1
USB_C_ESP32,J3,USB_C_Receptacle_G-Switch_GT-USB-7051x,C22464422,1
White LED,D7,LED_0805_2012Metric,C34499,1
Yellow LED,D4,LED_0805_2012Metric,C2296,1

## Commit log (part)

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2026-01-16 version final para mandar a pcbway
2026-01-16 agrego el README.md inicial con instrucciones
2026-01-17 Refactor: Renombrado de proyecto a DS para versionado semántico
2026-01-17 Fix: Eliminados archivos ignorados del repositorio
2026-01-17 Agregué advertencias
2026-01-17 actualizacion de .gitignore
2026-01-21 Se actualizaron algunas librerias del esquematico y se tomo nota de los errores de duplicación de uso de patas.
2026-01-22 Primer commit
2026-01-23 Ya generamos el primer ioc de stm32
2026-01-23 Add webserver files for DS Beamforming Control
    - Create requirements.txt with necessary dependencies for Flask and WebSocket support.
    - Add run.sh script to set up and run the Flask server with a virtual environment.
    - Implement CSS styles in style.css for a responsive and modern UI.
    - Develop main.js for frontend functionality, including WebSocket communication and device management.
    - Create index.html as the main template for the web interface, including device controls and logging.
2026-01-24 Version DS8 lista
2026-01-31 Add audio architecture and GPIO control documentation for DS Beamforming
    - Introduced `audio_architecture.md` detailing the audio system overview, components, clock synchronization, hardware configuration, audio flow for beamforming, initialization sequence, and verificat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
    - Added `gpio_control.md` outlining reserved GPIOs for system control, proposed functions for power button, error LED, audio activity LED, mute button, calibration mode, and speaker amplifier enable,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
2026-02-02 Remove lock file for KiCad schematic to prevent conflicts. New version sent to JLCPCB
2026-02-02 Add .DS_Store files to firmware directories
    - Added .DS_Store file to the firmware root directory.
    - Created .DS_Store file in the firmware/Core directory.
    - Created .DS_Store file in the firmware/Drivers directory.
2026-02-02 Add .gitignore file for C and C++ build artifacts
2026-02-02 Add .DS_Store to .gitignore to prevent tracking of macOS system files
2026-02-03 Add GPIO header file with function declarations for DS9 v2.0
    - Introduced gpio.h to define GPIO initialization, DAC, ADC, EEPROM, LED, and power control functions.
    - Functions include GPIO initialization for various peripherals, DAC control for reset and mute operations, ADC configuration, EEPROM write protection, LED control, and power management.
2026-02-13 New DS10 already under review. Errors corrected mostly on SAI ports mis addressed
2026-02-13 PowerSpecs acatualizado
2026-02-21 STM32 temp sensor working
2026-02-21 typo
2026-02-21 archivo de mas
2026-02-21 epaper module removed
2026-02-23 implementacion de dimmer leds
2026-03-19 Update README.md to reflect DS10 current architecture
    Rewrite from outdated DS7 description (TFT display, 2-layer PCB) to
    current DS10: 32-channel beamforming audio with integrated PAM8302A
    amps, AK5538VN ADC, 4-layer PCB, 24V power distribution, and Cat5e
    audio distribution for ~500 speaker installations.
2026-03-24 DS10: Add 24V power supply (MP2315S), PCB layout with 4-layer zones, fix AK5538VN bugs
    Power Supply:
    - MP2315S buck converter 24V→5V (3A, 500kHz, SOT-23-8)
    - T-type feedback network: R28(40.2k) + R26(7.5k) + R19(20k) for 5.03V output
    - AAM network: R12(9.09k) + R13(100k) for optimal PWM/PFM transition
    - EN divider: R29(470k) for 24V input
    - Output: 2x22µF ceramic (X5R, 16V, 1206), L1=4.9µH shielded inductor
2026-03-25 DS10: Fix critical bugs, complete design verification (570-net netlist)
    Critical fixes applied:
    - AK5538VN TDM mode: swapped TDM0/TDM1 pins (was TDM128, now TDM256)
    Pin 51 (TDM0) → GND, Pin 52 (TDM1) → +3V3
    - STM32 VBAT (U7/6): connected to +3V3 (was floating with only cap)
    - Reannotated all designators for consistent numbering
    Verified from complete 570-net netlist (no script crash):
2026-03-27 Agregue proteccion en la entrada de 24v, tambien un pullup para el booteo del esp32
